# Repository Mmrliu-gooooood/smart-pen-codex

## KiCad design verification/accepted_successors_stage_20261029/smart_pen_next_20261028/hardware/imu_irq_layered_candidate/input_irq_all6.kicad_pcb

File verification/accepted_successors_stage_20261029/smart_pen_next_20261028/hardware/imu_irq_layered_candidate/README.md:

# IRQ + MEMS 分层规则：有限范围可继续研究的原生板

**NOFAB，禁止据此下单生产或给未知相机接电。整笔和完整 IMU 接口尚未完成。**

本阶段只完成 `PICKUP_INT_N` 铜连接，并把经独立审查的 MEMS 分层规则实际合入。I²C 两网仍完全未布线，合计 4 项缺连接；没有把它们改成 NC，也没有换 GPIO、改源、绑模式或删除器件。

## 固定身份和实际结果

- 基线：`../j107_mode_port_closure`，PCB `8aa2581b4df112b979d83e67b9a6a2ddaa70a433c265cdc9849e41b60ff05ab5`。
- 本板：`native/mainboard_revD.kicad_pcb`，SHA-256 `752f83d57fa15450862dcf1c3751041b49f9830fd2c541443d717c6e99d1b229`。
- 102 个原生封装、356 个源端点、全部原生 footprint 块及原理图/项目/自定义规则树不变。10 个精确 Manufacturer/MPN/ProcurementStatus 字段随既有源版本保留并复核。
- 全量原生 DRC：**17 条违规 / 37 项未连 / 0 parity**，退出码 **5**。17 条完整违规 multiset 与基线完全相同，不只是计数碰巧相同。其中仍有 12 条错误（短路、孔/铜间距、阻焊桥）和 5 条 dangling 警告，绝非全板通过。
- 新鲜 ERC：0 错误，1 条原有 VBUS 边界 global-label warning；未通过静默排除改变门槛。
- 有限实铜图仅把 IRQ 两端合并；所有旧 pad 分量保持。AON 六个实填岛、GND 四个实填岛仍各有实铜路径到核心。
- normal / `python -O` 同一判定；5 类错误 × 两种模式均按预期错误类型拒绝。独立目录精确 delta 重放、再次完整填铜均再现上述 PCB SHA。

## 铜路径和小孔条件

IRQ 为 U101.6（GPIO1）到 U501.12（INT1）。所有新 IRQ 线宽仍 0.15 mm，未改为 FineSignal127。

**完整原生 IRQ：118.169488 mm / 86 段 / 3 个 via，28 段短于 0.1 mm。** 长度是铜中心线总和，不含焊盘内传播和 via 电气延迟。早期提及的 117.439382 mm 仅指长路径，另有 0.730106 mm MCU 扇出；不能把前者冒充整网长度。

长段主要在 In3，另有 B 面与两端 F 扇出；没有把 70 mm 信号放进 AON 电源层或地层。为释放 MCU 出口，只重排 BOOT 局部 F/In2 扇出：8 段旧铜移除、7 段 BOOT 新铜；BOOT via 从 (1.8,9.4) 移至 (1.26,9.7)，由 0.60/0.30 改为 **0.45/0.20 mm**。完整 BOOT 线段总长约 19.846068 → 20.430992 mm；所有 BOOT pad 的真实连接保留。

3 个 IRQ via 也为 0.45/0.20 mm 通孔。原项目允许的最小 via/钻孔/环宽为 0.45/0.20/0.10 mm；本孔理论环宽 0.125 mm，孔间距和孔铜间距门仍 0.25 mm。IRQ 保持 Default 0.15 mm 间距/线宽，没有改规则、盲孔或微孔。这是既有条件工艺内的局部小孔 override，**不代表厂家已批准叠层、钻孔、环宽、公差或报价**。

## MEMS 分层、必要外逃与参考地

依据 [ST TN0018 Rev.8 §3.9/3.10，图 15/16](https://www.st.com/resource/en/technical_note/tn0018-surface-mounting-guidelines-for-mems-sensors-in-an-lga-package-stmicroelectronics.pdf)，以及 `../mems_layered_rule_study`、`../mems_layered_independent_review` 与 `../../docs/electronics/mems_layered_rule_erratum`：

- F body 区 x3..5/y81..83 禁 pour/via，通孔穿 F 仍禁；中央 F 区实际禁 track。
- 内层参考铜按项目分层工程解释恢复，不再把旧“全部六层无平面”说成厂家要求。此解释不是六层应力/噪声或生产资格。
- 中央区范围是项目几何筛；y 边界含端排 pad 12.5 µm 重叠，**不能称精确全 pad 内缘**。允许原生 pad，本板新 IRQ 不进入中央禁穿越区。
- 新 IRQ 的 F 扇出在名义 body 内约 0.042863 mm²，其中 0.007569 mm² 在原生 pad 铜之外；它完全落在 pin12 向外必要接近带 x3.575..3.925/y81..81.2375 内。该原生 pad toe 距名义 body 边约 0.05 mm，不能制造“零交叠”而使正常连接不可实现。接近带是明确的项目解释，不是厂家给定的免审尺寸。旧外围 pad 横连、焊接/应力人工门仍保留。

`continuous_return_screen.json` 沿连续同层链合并检测，最大中心线参考投影缺口约 **0.383607 mm**；采样步长 ≤0.005 mm，边界采样不确定度说明为 0.010 mm。不同层的链不硬合并，换层另列；这不是返回电流仿真。F 参考 In1，In3/B 参考 In4；完整投影面积、各段缺口与所有 via 的近邻地 via 在 `reference_and_lengths.json`。

三个换层处到最近现有 GND via 的中心距约 2.7045、0.6915、2.9532 mm。尤其 IMU 端约 2.95 mm 的换层返回仍是电气/EMI门，不能靠 GND 同名或全岛连通免除。旧全层空白规则下 2.5483 mm 的参考缺口保存在 `historical_all6_reference.json`；本次合并恢复参考面后重新测量，并非继承分支通过。

## IRQ 的功能门仍未关闭

按 LIS2DW12 DS11811 Rev.9 §8.6，CTRL3 默认 push-pull、active-high、非锁存。**`PICKUP_INT_N` 的名字不会自动把硬件变成低有效。** 当前该网只有 MCU 与 INT1，没有外部上拉；不能假设改 open-drain 后已有偏置。

固件必须实际确认：输出极性/模式、INT1 路由、锁存与清除、睡前闲置电平、唤醒边沿/电平及休眠期间行为。尚未做唤醒/丢首笔实测；这里只证明限定静态铜连接，不证明首笔捕获、姿态补偿或产品功能。

## I²C 仍缺什么，以及拒绝了什么

SCL/SDA 的 10 kΩ 上拉、源端点和器件原位保留，仍各 3 个分离 pad，合计 4 项未连。时序预算引用 `../../docs/electronics/imu_i2c_timing_budget`：100 kHz 仅是待测首轮配置，不因低速就保证上升时间或总电容。

`rejected_comparisons.json` 和 `rejected_summaries/` 只保存精简反例：

- 低速控制改道释放两个 via，但 BOOT 的 In2 绕行切断核心 AON，拒绝；没有用细线救主电源。
- 单个 D0 换层能接回但没打开两线可行通道，未采用。
- HREF/VSYNC 靠边成组试验产生两出口，但返回空间不佳且源通道仍隔离，未采用。
- 6.87 mm BOOT In1 局部跳接切到 D0/D1 参考投影，拒绝；手工内侧版又撞 D1/D3 via。
- 带敏感 F 投影保护的小区域搜索未找到路径。这些都是有范围/采样精度的失败试验，**不是全板绝无可行布局的数学证明**。

下一步需要连同多网 MCU 扇出一起重新分配，不继续在拥挤版上逐点添加救线。所有这些失败 trial 的铜、位置和规则均不在本板内。

## 复验与边界

```bash
/usr/bin/python3 build.py --output /tmp/new-empty-irq-native
/usr/bin/python3 verify.py
/usr/bin/python3 -O verify.py
/usr/bin/python3 negative_tests.py
/usr/bin/python3 replay_and_refill.py
/usr/bin/python3 pcb_preflight.py native/mainboard_revD.kicad_pcb --lock preflight_lock.json --report preflight.json --run-drc
```

最后一项预期退出 5，而不是假造通过。冻结目录不可原地重跑写报告脚本，应先复制到新的隔离目录。`dependencies.json` 绑定必要历史 manifest；没有整包复制移动 trial。

JP301 与充电 commissioning 保持 OPEN，未知定制相机仍隔离；TPS22918 不是过流限流保护。RF、真实叠层与钻孔 DFM、回流/PI、换层 EMI、I²C、机械线束、剩余全板错误及成本报价均未关闭。本阶段没有采购、通电、发布或 GitHub 写入。

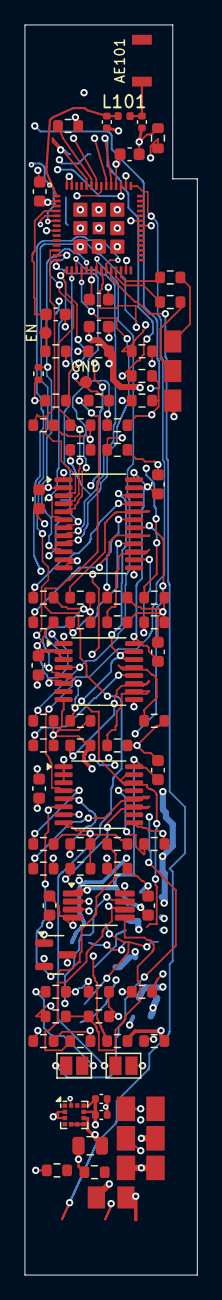
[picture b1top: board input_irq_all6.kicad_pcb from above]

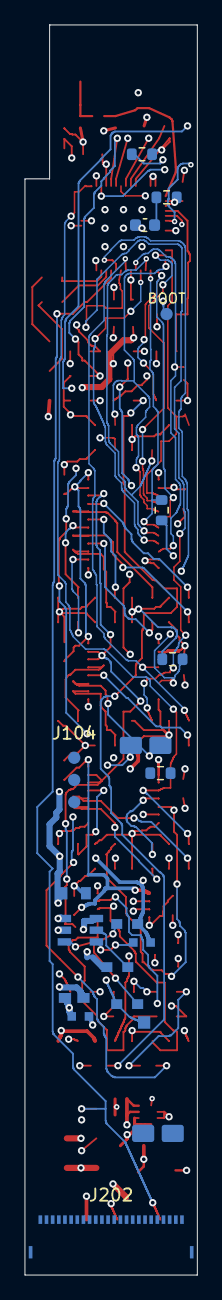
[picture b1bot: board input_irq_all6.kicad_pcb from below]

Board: 6 copper layers, 14.0 x 101.5 mm, 102 parts (19 on the bottom side), 70 nets.

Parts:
AE101: 2450AT18A0100001E_STUDY_NOFAB; Johanson_2450AT18A0100001E_Rev4_Study_NOFAB
C101: 1u; C_0603_1608Metric
C102: 22u; C_0603_1608Metric
C103, C104, C105: 100n; C_0603_1608Metric
C106, C107: DNP RF_TUNE; C_0402_1005Metric
C201, C202, C203, C204, C205, C206, C207, C208: 100n X7R; C_0603_1608Metric
C301: 10uF 10V X7R; C1_TDK_0805_X7R_STANDARD
C302: 1uF 10V X7R; C2_TDK_0603_STUDY
C303: 1nF 25V C0G; C3_TDK_0603_STUDY
C501, C502: 100nF 16V X7R +/-10%; C_0402_1005Metric
C503: 10uF 10V X7R +/-10%; C_0805_2012Metric
C504: 1n C0G; C_0603_1608Metric
J103: DRY CONTACT PADS; WireLands2_P2.4
J104: UART_SERVICE_CAMERA_OFF_ONLY; Probe3_P1.8_NoPaste
J105: ADC_SAFE_FRONTEND_LINK_NOT_RAW_BATTERY; WireLands2_P2.4
J106: POWER_CORE; J106_Wirebank_PRELAYOUT
J107: CHARGER_MODE; J107_Wirebank_PRELAYOUT
J108: SERVICE_EN_BOOT_GND; ServiceProbe3_NOFAB
J109: USB_TAIL_LINK; USBWireLands3_14mm_PRELAYOUT
J202: 5034802400_NEW_24PIN_SENSOR_HANDOFF; Molex_5034802400_24P_P0.5_CANDIDATE
J301: APPROVED LOAD / TBD; J301_Wirebank_PRELAYOUT
JP201: DNP_IO_COMMISSION; SolderJumper-2_P1.3mm_Open_Pad1.0x1.5mm
JP202: DNP_SCCB_COMMISSION; SolderJumper-2_P1.3mm_Open_Pad1.0x1.5mm
JP301: OPEN / DO NOT BRIDGE; Commission_OPEN_NO_PASTE
L101: RF_MATCH_TBD; L_0402_1005Metric
Q201: PMV30UN2; SOT-23
R101, R102, R103, R104, R105, R203, R206, R207, R501, R502: 10k 1%; R_0603_1608Metric
R106, R107, R108, R109, R202, R210, R211, R212, R213, R214, R215, R216, R218, R219, R220, R221, R222, R223, R224, R225, R226, R227, R228, R229, R230, R231, R232, R233, R234, R235, R237, R503: 100k 1%; R_0603_1608Metric
R112, R113: 22R SI_TBD; R_0603_1608Metric
R201, R504: 1k 1%; R_0603_1608Metric
R204: 100R 1%; R_0603_1608Metric
R205: 4.7k 1%; R_0603_1608Metric
R217: 100k 1%; R_0402_1005Metric
R236: 4.7k 1% RESET_CANDIDATE; R_0603_1608Metric
R240, R241, R242, R243: 10k 1% INITIAL_100kHz; R_0603_1608Metric
R301: 100k 1%; R1_YAGEO_0603_STUDY
R302: 1k 1%; R2_YAGEO_0603_STUDY
R303: 100R 1%; R3_YAGEO_0603_STUDY
TP301: ENABLE MEASURE; Enable_measure_land
U101: ESP32-S3-PICO-1-N8R8; ESP32-S3-PICO-1_LGA57_7x7_P0.4_OfficialDerived_NOFAB
U201: SN74AXC8T245PWR; TSSOP-24_4.4x7.8mm_P0.65mm
U202, U203: SN74AXC4T245PWR; TSSOP-16_4.4x5mm_P0.65mm
U204: TCA9517DGKR; VSSOP-8_3x3mm_P0.65mm
U301: TPS22918DBVR; TPS22918_DBV_TI_1p1x0p6
U501: LIS2DW12TR; LGA-12_2x2mm_P0.5mm

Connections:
3V3_AON: C102.1, C103.1, C104.1, C105.1, C201.1, C203.1, C205.1, C207.1, C301.1, C501.1, C502.1, C503.1, J106.2, R101.2, R102.2, R103.2, R203.2, R240.2, R241.2, R501.1, R502.1, R503.1, U101.2, U101.3, U101.20, U101.46, U101.55, U101.56, U201.1, U202.1, U203.1, U203.2, U203.3, U204.8, U301.1, U501.2, U501.3, U501.9, U501.10
AON_I2C_SCL: R501.2, U101.10, U501.1
AON_I2C_SDA: R502.2, U101.11, U501.4
BATTERY_ADC: J105.1, U101.9
BOOT_N: J108.2, R102.1, U101.5
CAM_3V3_PRELINK: C302.1, JP301.1, R303.1, U301.6
CAM_3V3_SW: J301.1, JP301.2
CAM_BUS_EN: JP202.1, R108.1, U101.37
CAM_CT: C303.1, U301.4
CAM_D0: R210.1, U101.12, U201.3
CAM_D1: R211.1, U101.13, U201.4
CAM_D2: R212.1, U101.14, U201.5
CAM_D3: R213.1, U101.15, U201.6
CAM_D4: R214.1, U101.16, U201.7
CAM_D5: R215.1, U101.17, U201.8
CAM_D6: R216.1, U101.18, U201.9
CAM_D7: R217.1, U101.19, U201.10
CAM_HREF: R220.1, U101.23, U202.6
CAM_IO_EN: JP201.1, R107.1, U101.48
CAM_ISO_OE_N: Q201.3, R203.1, U201.22, U202.14, U202.15, U203.14, U203.15
CAM_ON: R301.1, R302.2, U301.3
CAM_PCLK: R218.1, U101.21, U202.4
CAM_PWDN_UART_RX: J104.2, R223.1, U101.50, U203.6
CAM_PWR_EN: R106.1, R302.1, TP301.1, U101.47
CAM_QOD: R303.2, U301.5
CAM_RESET_UART_TX: J104.1, R222.1, U101.49, U203.5
CAM_SCL: R240.1, U101.44, U204.7
CAM_SDA: R241.1, U101.45, U204.6
CAM_VSYNC: R219.1, U101.22, U202.5
CAM_XCLK: R221.1, U101.43, U203.4
CHIP_EN: C101.1, J108.1, R101.1, U101.4
CONTACT: J103.1, R504.2
GND: C101.2, C102.2, C103.2, C104.2, C105.2, C106.2, C107.2, C201.2, C202.2, C203.2, C204.2, C205.2, C206.2, C207.2, C208.2, C301.2, C302.2, C303.2, C501.2, C502.2, C503.2, C504.2, J103.2, J104.3, J105.2, J106.3, J107.3, J108.3, J109.3, J202.1, J202.4, J202.7, J202.10, J202.13, J202.17, J202.24, J301.2, Q201.2, R104.2, R105.2, R106.2, R107.2, R108.2, R109.2, R202.2, R205.2, R206.2, R207.2, R210.2, R211.2, R212.2, R213.2, R214.2, R215.2, R216.2, R217.2, R218.2, R219.2, R220.2, R221.2, R222.2, R223.2, R224.2, R225.2, R226.2, R227.2, R228.2, R229.2, R230.2, R231.2, R232.2, R233.2, R234.2, R235.2, R236.2, R237.2, R301.2, U101.57, U201.2, U201.11, U201.12, U201.13, U202.2, U202.3, U202.8, U202.9, U203.8, U203.9, U204.4, U301.2, U501.5, U501.6, U501.7, U501.8
ILLUM_STROBE: R109.1, U101.36
IO_ENABLE_LINK: JP201.2, R201.1
ISO_GATE: Q201.1, R201.2, R202.1
NIB_CONTACT_N: C504.1, R503.2, R504.1, U101.7
PICKUP_INT_N: U101.6, U501.12
RF_ANT: AE101.1, C107.1, L101.2
RF_SIP: C106.1, L101.1, U101.1
SCCB_ENABLE_LINK: JP202.2, R204.1
SCCB_EN_SAFE: R204.2, R205.1, U204.5
SENS_D0: J202.2, R224.1, U201.21
SENS_D1: J202.3, R225.1, U201.20
SENS_D2: J202.5, R226.1, U201.19
SENS_D3: J202.6, R227.1, U201.18
SENS_D4: J202.8, R228.1, U201.17
SENS_D5: J202.9, R229.1, U201.16
SENS_D6: J202.11, R230.1, U201.15
SENS_D7: J202.12, R231.1, U201.14
SENS_EXTCLK: J202.18, R235.1, U203.13
SENS_HREF: J202.16, R234.1, U202.11
SENS_PCLK: J202.14, R232.1, U202.13
SENS_SCL: J202.21, R242.1, U204.2
SENS_SDA: J202.22, R243.1, U204.3
SENS_TRIG_IN: J202.20, R237.1, U203.11
SENS_VIO_1V8: C202.1, C204.1, C206.1, C208.1, J202.23, R242.2, R243.2, U201.23, U201.24, U202.16, U203.16, U204.1
SENS_VSYNC: J202.15, R233.1, U202.12
SENS_XSHUTDN_N: J202.19, R236.1, U203.12
STRAP_GPIO3: R103.1, U101.8
STRAP_GPIO45: R104.1, U101.51
STRAP_GPIO46: R105.1, U101.52
UNUSED_A_INPUT: R207.1, U203.7
UNUSED_B_INPUT: R206.1, U202.10
USB_DM: J109.2, R113.1
USB_DM_MCU: R113.2, U101.25
USB_DP: J109.1, R112.1
USB_DP_MCU: R112.2, U101.26
USB_EN1: J107.1, U101.24
USB_EN2: J107.2, U101.27
